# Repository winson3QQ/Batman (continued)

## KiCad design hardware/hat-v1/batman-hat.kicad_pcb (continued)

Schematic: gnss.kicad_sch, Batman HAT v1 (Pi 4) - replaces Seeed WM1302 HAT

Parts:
C80: 10u 10V; C_0603_1608Metric
C81: 100n 16V; C_0402_1005Metric
C82: 10n 16V; C_0402_1005Metric
C83: 47p C0G; C_0402_1005Metric
J4: U.FL; U.FL_Hirose_U.FL-R-SMT-1_Vertical; MPN U.FL-R-SMT-1(10)
JP6: GNSS (closed); SolderJumper-2_P1.3mm_Bridged_RoundedPad1.0x1.5mm
L80: 27nH; L_0402_1005Metric; MPN LQG15HS27NJ02D
R80: DNP 0R; R_0402_1005Metric; not fitted
R81: 68R; R_1206_3216Metric
U14: MAX-M10S-00B; ublox_MAX; MPN MAX-M10S-00B; not fitted

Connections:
3V3_GNSS: C80.1, C81.1, JP6.2, U14.6 (V_BCKP), U14.7 (VCC_IO), U14.8 (VCC); also elsewhere on the board
GND: C80.2, C81.2, C82.2, J4.2 (SHIELD), R80.2, U14.1 (GND), U14.10 (GND), U14.12 (GND); also elsewhere on the board
GNSS_ANT: C83.1, J4.1 (SIG), L80.2
GNSS_ANT_DET: U14.16 (SDA); also elsewhere on the board
GNSS_ANT_FEED: C82.1, L80.1, R81.2; also elsewhere on the board
GNSS_ANT_SHORT_N: U14.17 (SCL); also elsewhere on the board
GNSS_ANT_SUP: R81.1, U14.14 (VCC_RF); also elsewhere on the board
GNSS_LNA_EN: U14.13 (LNA_EN); also elsewhere on the board
GNSS_PPS: U14.4 (TIMEPULSE); also elsewhere on the board
GNSS_RFIN: C83.2, U14.11 (RF_IN)
GNSS_RST_N: U14.9 (~RESET); also elsewhere on the board
GNSS_SAFEBOOT_N: U14.18 (~SAFEBOOT); also elsewhere on the board
GNSS_VIOSEL: R80.1, U14.15 (VIO_SEL)
UART5_RX: U14.2 (TXD); also elsewhere on the board
UART5_TX: U14.3 (RXD); also elsewhere on the board

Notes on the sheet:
NOTES JP6: cut to isolate the GNSS supply (UART5_TX idle-high still back-feeds RXD) U14: UBX-20035208 R08: VIO_SEL open = 3.3 V I/O; V_BCKP 1.65-3.6 V; V_IO ramp >= 25 us/V; ext. gain <= 30 dB R80: leave NOT fitted: VIO_SEL to GND would select 1.8 V I/O (datasheet Table 10) R81: VCC_RF max 50 mA op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

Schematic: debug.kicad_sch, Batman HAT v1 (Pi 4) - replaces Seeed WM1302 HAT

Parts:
J5: Tag-Connect TC2050; Tag-Connect_TC2050-IDC-NL_2x05_P1.27mm_Vertical
R40, R41, R42, R43, R44, R45, R46, R47: 0R; R_0402_1005Metric
R48: 1k; R_0402_1005Metric
TP1: VBAT 6-17V; TestPoint_Keystone_5015_Micro-Minature
TP2: 5V 5.10-5.25; TestPoint_Keystone_5015_Micro-Minature
TP3: 3V3 HaLow 3.2-3.4; TestPoint_Keystone_5015_Micro-Minature
TP4: GND; TestPoint_Keystone_5015_Micro-Minature
TP5: VSYS 6-17V; TestPoint_Pad_D1.5mm
TP6: 5V_PI 5.0-5.2; TestPoint_Pad_D1.5mm
TP7: 3V3_BUCK 3.25-3.40; TestPoint_Pad_D1.5mm
TP8: 3V3_PI 3.2-3.4; TestPoint_Pad_D1.5mm
TP9: 3V3_SEC 3.2-3.4; TestPoint_Pad_D1.5mm
TP10: 3V3_GNSS 3.2-3.4; TestPoint_Pad_D1.5mm
TP11: VRTC 0-3.3; TestPoint_Pad_D1.5mm
TP12: GND; TestPoint_Pad_D1.5mm
TP13: GNSS_RST_N; TestPoint_Pad_D1.0mm
TP14: GNSS_SAFEBOOT_N; TestPoint_Pad_D1.0mm
TP15: GNSS_ANT_DET; TestPoint_Pad_D1.0mm
TP16: GNSS_ANT_SHORT_N; TestPoint_Pad_D1.0mm
TP17: PWR_BTN_N; TestPoint_Pad_D1.0mm
TP18: LTC_KILL_N; TestPoint_Pad_D1.0mm
TP19: LTC_ENB; TestPoint_Pad_D1.0mm
TP20: EN_5V; TestPoint_Pad_D1.0mm
TP21: EN_3V3; TestPoint_Pad_D1.0mm
TP22: PG_5V; TestPoint_Pad_D1.0mm
TP23: EF_FLT_N; TestPoint_Pad_D1.0mm
TP24: EF_SHDN; TestPoint_Pad_D1.0mm
TP25: RTC_CLKOUT; TestPoint_Pad_D1.0mm
TP26: RTC_INT_N; TestPoint_Pad_D1.0mm
TP27: K1+ (R9); TestPoint_Pad_D1.0mm
TP28: K1- (R9); TestPoint_Pad_D1.0mm
TP29: K2+ (R22); TestPoint_Pad_D1.0mm
TP30: K2- (R22); TestPoint_Pad_D1.0mm

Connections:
3V3_BUCK: TP7.1, TP29.1; also elsewhere on the board
3V3_GNSS: TP10.1; also elsewhere on the board
3V3_MPCIE: TP3.1; also elsewhere on the board
3V3_SEC: TP9.1; also elsewhere on the board
3V3_SH: TP30.1; also elsewhere on the board
5V_BUCK: TP2.1; also elsewhere on the board
CONSOLE_RX: R41.1; also elsewhere on the board
CONSOLE_TX: R40.1; also elsewhere on the board
EF_FLT_N: TP23.1; also elsewhere on the board
EF_OUT: TP27.1; also elsewhere on the board
EF_SHDN: TP24.1; also elsewhere on the board
EN_5V: TP20.1; also elsewhere on the board
GND: J5.3, TP4.1, TP12.1; also elsewhere on the board
GNSS_ANT_DET: TP15.1; also elsewhere on the board
GNSS_ANT_SHORT_N: TP16.1; also elsewhere on the board
GNSS_RST_N: TP13.1; also elsewhere on the board
GNSS_SAFEBOOT_N: TP14.1; also elsewhere on the board
HALOW_BUSY: R47.1; also elsewhere on the board
HALOW_IRQ: R46.1; also elsewhere on the board
LTC_ENB: TP19.1; also elsewhere on the board
LTC_KILL_N: TP18.1; also elsewhere on the board
PG_5V: TP22.1; also elsewhere on the board
PWR_BTN_N: TP17.1; also elsewhere on the board
RTC_CLKOUT: TP25.1; also elsewhere on the board
RTC_INT_N: TP26.1; also elsewhere on the board
SPI0_CE0: R45.1; also elsewhere on the board
SPI0_MISO: R44.1; also elsewhere on the board
SPI0_MOSI: R43.1; also elsewhere on the board
SPI0_SCLK: R42.1; also elsewhere on the board
TC_3V3: J5.1, R48.2
TC_BUSY: J5.10, R47.2
TC_CS: J5.8, R45.2
TC_IRQ: J5.9, R46.2
TC_MISO: J5.7, R44.2
TC_MOSI: J5.6, R43.2
TC_RX: J5.4, R41.2
TC_SCLK: J5.5, R42.2
TC_TX: J5.2, R40.2
VBAT_RAW: TP1.1; also elsewhere on the board
VRTC: TP11.1; also elsewhere on the board
VSYS: TP5.1, TP28.1; also elsewhere on the board

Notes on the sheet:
NOTES J5: console = passwordless root until #137 ships: release gate R48: sense only: an adapter that drives VCC cannot back-feed the Pi R40: R40-R47 debug links: fitted on dev boards, NOT fitted on production (HaLow keys cross SPI0) TP27: Kelvin pads on the shunts: R9 mV x 100 = mA, R22 mV x 50 = 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

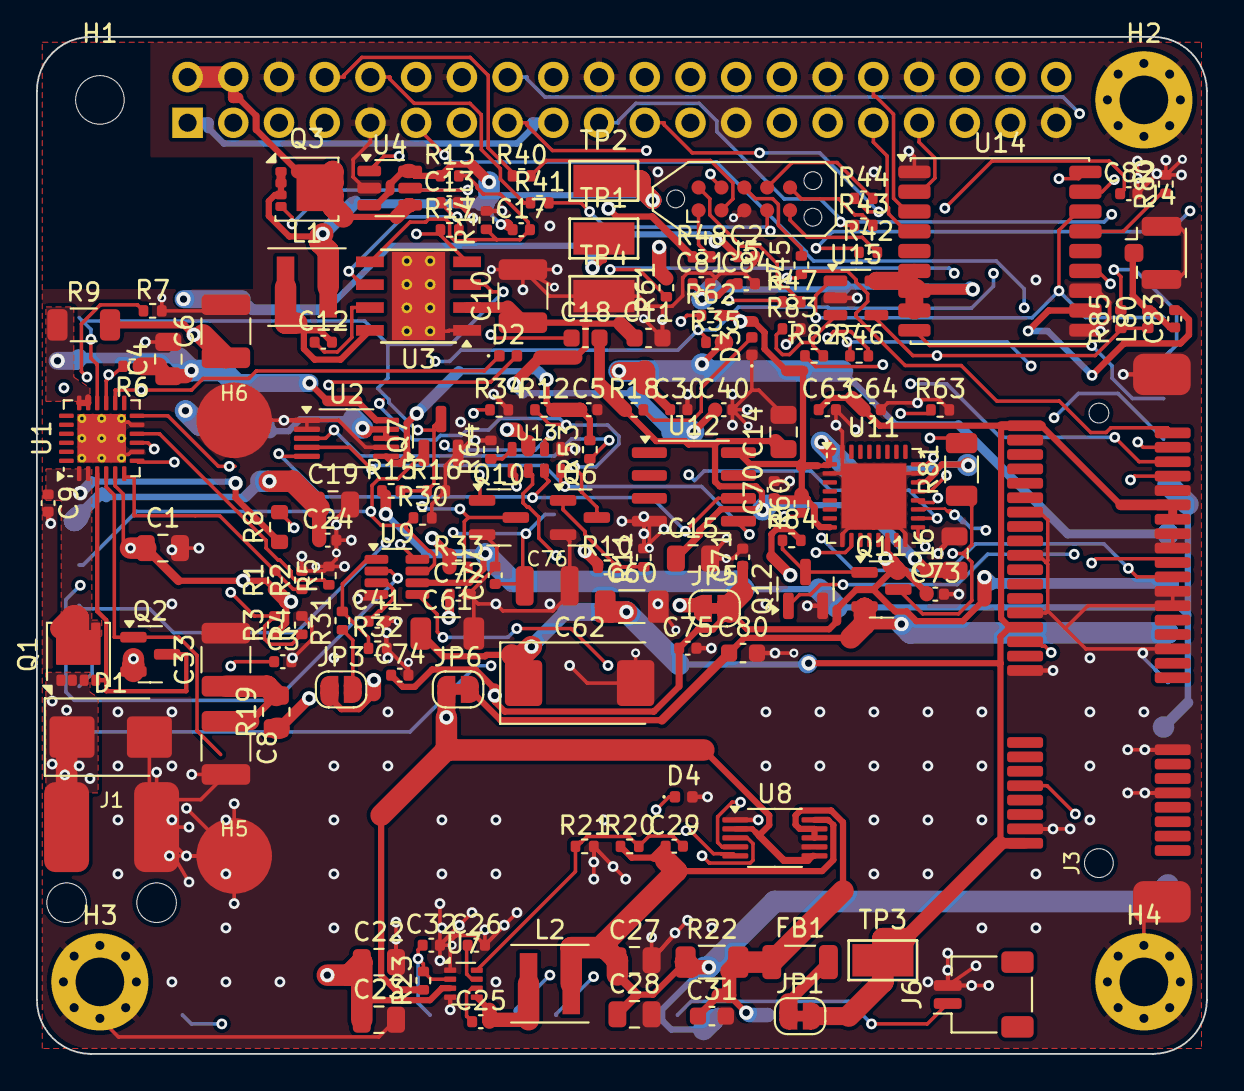
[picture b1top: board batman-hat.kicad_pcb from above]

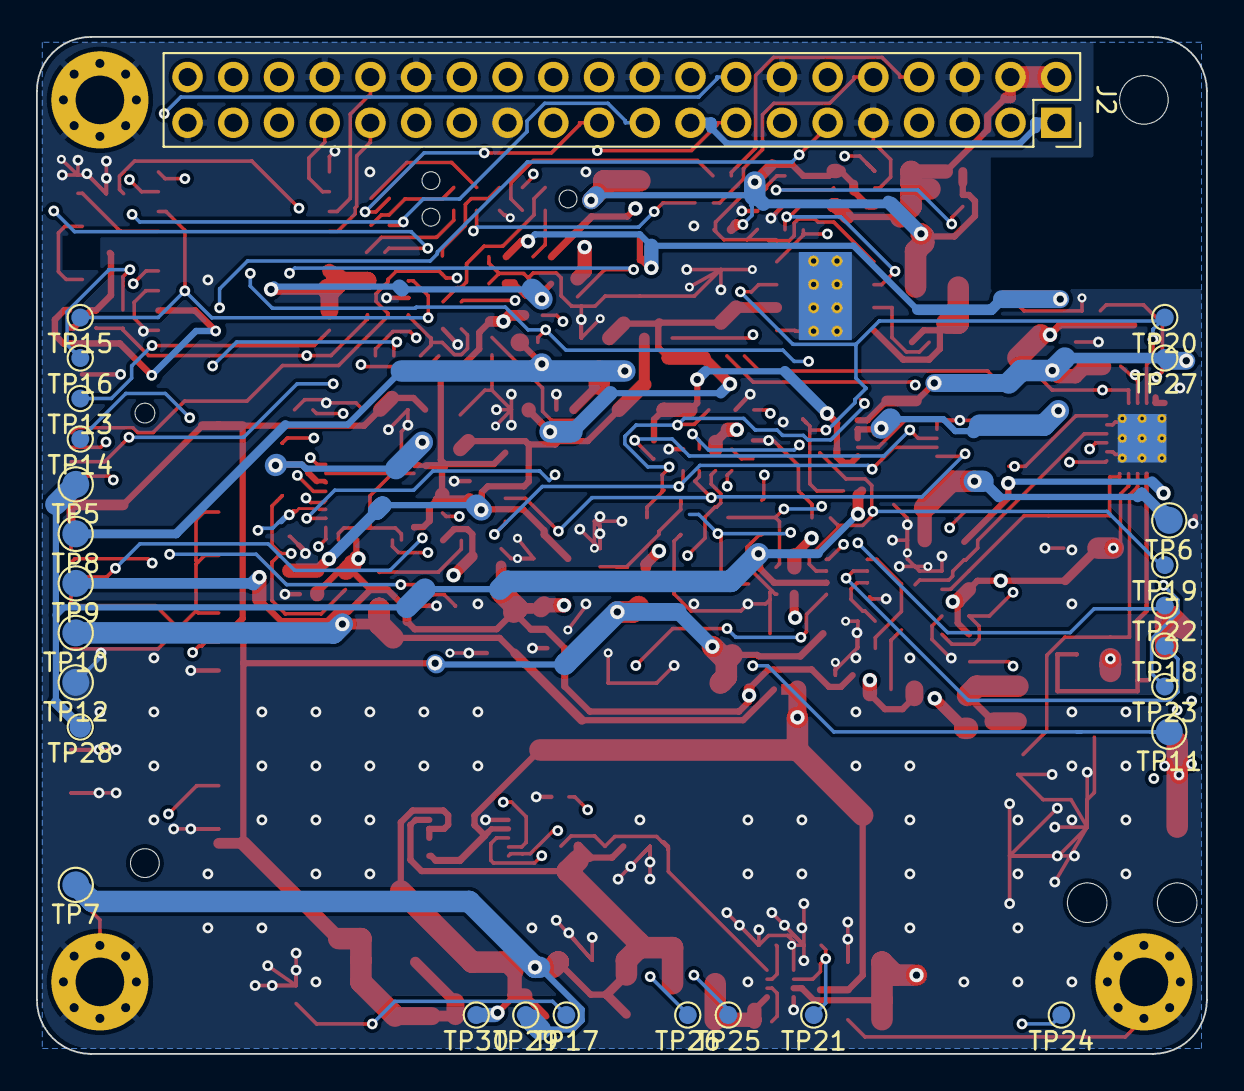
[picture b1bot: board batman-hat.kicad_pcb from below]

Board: 4 copper layers, 65.0 x 56.5 mm, 174 parts (27 on the bottom side), 97 nets.

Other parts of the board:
C84: 100n 16V; C_0402_1005Metric
Q11: Si2301CDS; SOT-23
Q12: BSS138; SOT-23
R82: 560R; R_0402_1005Metric
R83, R84: 100k; R_0402_1005Metric
R85: 1k; R_0402_1005Metric
U15: OPA333AIDBVR; SOT-23-5

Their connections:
3V3_GNSS: C84.1, Q11.2, R84.2, U15.5; also elsewhere on the board
GND: C84.2, Q12.2, R83.2, U15.2; also elsewhere on the board
GNSS_ANT_DET: U15.1; also elsewhere on the board
GNSS_ANT_FEED: R85.1, U15.4; also elsewhere on the board
GNSS_ANT_SHORT_N: R85.2; also elsewhere on the board
GNSS_ANT_SUP: Q11.3, R82.1; also elsewhere on the board
GNSS_ANT_VREF: R82.2, R83.1, U15.3
GNSS_LNA_EN: Q12.1; also elsewhere on the board
GNSS_T1G: Q11.1, Q12.3, R84.1

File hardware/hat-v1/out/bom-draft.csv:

Refs,Qty,Value,Footprint,MPN,Manufacturer,Tier,LCSC,Assembly,Note
"C1,C4",2,1u 50V X7R,C_0805_2012Metric,,,C,,JLCPCB,
"C2,C9,C40",3,100n 50V X7R,C_0402_1005Metric,,,C,,JLCPCB,
C3,1,22n 16V X7R,C_0402_1005Metric,,,C,,JLCPCB,2.27 V/ms soft start
"C5,C12,C24,C25,C30,C63,C64,C70,C71,C72,C74,C75,C77,C81,C84",15,100n 16V,C_0402_1005Metric,,,C,,JLCPCB,
"C6,C8,C10,C33",4,10u 50V X7R,C_1210_3225Metric,,,C,,JLCPCB,
C11,1,220n 50V X7R,C_0603_1608Metric,,,C,,JLCPCB,hot-loop cap: closest to VIN/PGND
"C13,C41,C73",3,1u 10V,C_0402_1005Metric,,,C,,JLCPCB,
"C14,C15,C16,C19,C22,C23,C27,C28",8,22u 10V X5R,C_0805_2012Metric,,,C,,JLCPCB,
"C17,C29",2,DNP 22p,C_0402_1005Metric,,,C,,DNP,optional feed-forward (datasheet 9.2.2.8)
C18,1,220n 25V X7R,C_0603_1608Metric,,,C,,JLCPCB,
C26,1,22n 16V,C_0402_1005Metric,,,C,,JLCPCB,soft start ~3.2 ms
C31,1,10u 10V X5R,C_0603_1608Metric,,,C,,JLCPCB,pi-filter input cap
C32,1,2.2n 16V,C_0402_1005Metric,,,C,,JLCPCB,EN has only a 0.7 uA pull-up: noise immunity
"C60,C61",2,47u 6.3V X5R,C_1206_3216Metric,,,C,,JLCPCB,
C62,1,220u 6.3V polymer,CP_EIA-7343-20_Kemet-V,T520V227M006ATE015,KEMET,C,,JLCPCB,7343-20: <=1.9 mm tall; absorbs HaLow TX bursts
C76,1,CPH3225A 11mF,Seiko_CPH3225A,CPH3225A,Seiko Instruments,C,,JLCPCB,"RTC backup (user decision 2026-09-27: supercap, GPS re-syncs after ~2 days off). Internal trickle path has a Schottky (0.25 V) -> charges to ~3.05 V, below the 3.3 V rating"
C80,1,10u 10V,C_0603_1608Metric,,,C,,JLCPCB,
C82,1,10n 16V X7R,C_0402_1005Metric,,,C,,JLCPCB,C14: bias-T capacitor (Table 52)
C83,1,47p C0G,C_0402_1005Metric,,,C,,JLCPCB,C18: DC block 47 pF 5 % C0G (Table 52)
D1,1,SMBJ20CA,D_SMB,SMBJ20CA,Littelfuse,C,,JLCPCB,bidirectional: survives reversed battery
D2,1,RED,LED_0402_1005Metric,,,C,,JLCPCB,eFuse fault LED (on = fault)
D3,1,GREEN,LED_0402_1005Metric,,,C,,JLCPCB,HAT 5 V buck running
D4,1,TPD1E10B06,D_0402_1005Metric,TPD1E10B06DPYR,TI,C,,JLCPCB,ESD for the panel button wire
FB1,1,600R@100MHz >=4A,L_1206_3216Metric,BLM31KN601SN1L,Murata,C,,JLCPCB,"verify rating at BOM step: >=4 A, <=30 mOhm"
J2,1,"Pi 40-pin (female, 11 mm stack)",PinSocket_2x20_P2.54mm_Vertical,,,C,,JLCPCB,through-hole on the bottom side; 8.5 mm socket for 11 mm standoffs
J3,1,mPCIe 5.2H,MiniPCIe_Lianxin_XDMP-052-A01_H5.2,XDMP-052-A01,Lianxin (China),C,C7498130,JLCPCB,pin 8 UIM_PWR not connected on the card -> GPIO18 freed for the TPM
J4,1,U.FL,U.FL_Hirose_U.FL-R-SMT-1_Vertical,U.FL-R-SMT-1(10),Hirose,C,,JLCPCB,active patch antenna with SAW pre-filter; 50 ohm CPWG trace
J6,1,PANEL BTN,JST_SH_SM02B-SRSS-TB_1x02-1MP_P1.00mm_Horizontal,SM02B-SRSS-TB,JST,C,,JLCPCB,to the IP67 panel push-button. No on-board button (user decision): on the bench plug a button here or short the PWR_BTN_N back-side pad to GND
L1,1,3.3uH Isat>=5.5A,L_Coilcraft_XxL4030,XGL4030-332MEC,Coilcraft,C,,JLCPCB,height <=3.1 mm; alternative: Wurth WE-XHMI 4030
L2,1,2.2uH Isat>=5.8A,L_Coilcraft_XxL4030,XGL4030-222MEC,Coilcraft,C,,JLCPCB,
L80,1,27nH,L_0402_1005Metric,LQG15HS27NJ02D,Murata,C,,JLCPCB,"L3: bias-T inductor, >500 ohm at L1, >=300 mA (Table 54)"
Q1,1,CSD19537Q3,VSON-8_3.3x3.3mm_P0.65mm_NexFET,CSD19537Q3,TI,C,,JLCPCB,reverse-polarity blocking FET (TPS2663 datasheet Fig 9-2)
"Q2,Q6,Q7,Q10,Q12",5,BSS138,SOT-23,BSS138,onsemi (not Nexperia),C,,JLCPCB,"B_GATE fast pull-down: Vds>=15V, Vgs max 20V, Ciss<=50pF, Vth(min)<=3V"
Q3,1,CSD17578Q3A,VSON-8_3.3x3.3mm_P0.65mm_NexFET,CSD17578Q3A,TI,C,,JLCPCB,"30 V, low Rds(on); ideal-diode FET"
Q11,1,Si2301CDS,SOT-23,SI2301CDS-T1-GE3,Vishay,C,,JLCPCB,T1: antenna supply switch (reference uses Vishay Si1016X; any small P-FET)
"R1,R6",2,383k 1%,R_0402_1005Metric,,,C,,JLCPCB,
"R2,R4,R7,R32",4,100k 1%,R_0402_1005Metric,,,C,,JLCPCB,
R3,1,1.50M 1%,R_0402_1005Metric,,,C,,JLCPCB,"OVP 19.2 V typ (18.8-19.6), release >=17.44 V: full 4S 16.8 V never latches off (review P3)"
R5,1,3.57k 1%,R_0402_1005Metric,,,C,,JLCPCB,I_OL = 18k/R = 5.0 A
R8,1,4.7k,R_0603_1608Metric,,,C,,JLCPCB,LED fed from EF_IN: protected from reverse battery
R9,1,10m 1% 0.5W,R_1206_3216Metric,,,C,,JLCPCB,INA226 #1 shunt; route IN+/IN- as Kelvin traces from the pads
"R10,R11,R30",3,1M,R_0402_1005Metric,,,C,,JLCPCB,1M/1M: 9 uA standby drain
"R12,R33,R35,R53,R60,R61,R62,R63",8,10k,R_0402_1005Metric,,,C,,JLCPCB,
R13,1,100k 0.5%,R_0402_1005Metric,,,C,,JLCPCB,
R14,1,24.0k 0.5%,R_0402_1005Metric,,,C,,JLCPCB,Vout = 1.0 V x (1 + 100/24) = 5.17 V
R15,1,102k 1%,R_0402_1005Metric,,,C,,JLCPCB,
R16,1,24.3k 1%,R_0402_1005Metric,,,C,,JLCPCB,EN UVLO: 6.40 V on / 5.88 V off
"R17,R23,R34,R64,R83,R84",6,100k,R_0402_1005Metric,,,C,,JLCPCB,
R18,1,2.2k,R_0402_1005Metric,,,C,,JLCPCB,
R19,1,0.47R,R_0805_2012Metric,,,C,,JLCPCB,RC damper for hot-plug ringing: 0.47R + 2x10uF keeps a 16.8 V plug-in below OVP (sim S1)
R20,1,31.6k 1%,R_0402_1005Metric,,,C,,JLCPCB,
R21,1,10.0k 1%,R_0402_1005Metric,,,C,,JLCPCB,Vout = 0.8 V x (1 + 31.6/10) = 3.33 V
R22,1,20m 1% 0.5W,R_1206_3216Metric,,,C,,JLCPCB,"INA226 #2 shunt, upstream of every socket bulk cap"
R31,1,787k 1%,R_0402_1005Metric,,,C,,JLCPCB,AUTO-ON 7.10 V typ / 6.74 V min: above the 5 V buck EN max 6.55 V (review P1)
"R40,R41,R42,R43,R44,R45,R46,R47",8,0R,R_0402_1005Metric,,,C,,JLCPCB,"R40-R47 debug links: fitted on dev boards, NOT fitted on production (HaLow keys cross SPI0)"
"R48,R85",2,1k,R_0402_1005Metric,,,C,,JLCPCB,sense only: an adapter that drives VCC cannot back-feed the Pi
R80,1,DNP 0R,R_0402_1005Metric,,,C,,DNP,leave NOT fitted: VIO_SEL to GND would select 1.8 V I/O (datasheet Table 10)
R81,1,10R,R_1206_3216Metric,,,C,,JLCPCB,R8: current sense / short limiter 10 ohm 0.25 W (Table 53); ~18.5 mV per 1.85 mA
R82,1,560R,R_0402_1005Metric,,,C,,JLCPCB,R5 (Table 53)
TP1,1,VBAT 6-17V,TestPoint_Keystone_5015_Micro-Minature,,,C,,JLCPCB,
TP2,1,5V 5.10-5.25,TestPoint_Keystone_5015_Micro-Minature,,,C,,JLCPCB,
TP3,1,3V3 HaLow 3.2-3.4,TestPoint_Keystone_5015_Micro-Minature,,,C,,JLCPCB,
TP4,1,GND,TestPoint_Keystone_5015_Micro-Minature,,,C,,JLCPCB,
U1,1,TPS26631RGER,Texas_RGE0024H_VQFN-24-1EP_4x4mm_P0.5mm_EP2.7x2.7mm_ThermalVias,TPS26631RGER,TI,B,,JLCPCB,MODE=GND auto-retry; SHDN floats (2.7 V open-circuit) = enabled; IMON unused
"U2,U8",2,INA226AIDGSR,VSSOP-10_3x3mm_P0.5mm,INA226AIDGSR,TI,B,,JLCPCB,I2C 0x40 (A0=A1=GND): whole-node current + battery voltage
U3,1,LMR33640DDDAR,Texas_HSOP-8-1EP_3.9x4.9mm_P1.27mm_ThermalVias,LMR33640DDDAR,TI,B,,JLCPCB,"1 MHz, 4 A"
U4,1,LM74700QDBVRQ1,SOT-23-6,LM74700QDBVRQ1,TI,B,,JLCPCB,HAT back-power rule: Pi USB-C cannot feed into the HAT 5 V buck
U7,1,TPS62933FDRLR,SOT-583-8,TPS62933FDRLR,TI,B,,JLCPCB,FCCM fixed 1.2 MHz (RT=GND); EN abs max 6 V -> open-drain pull-down only
U9,1,LTC2955ITS8-2#TRPBF,TSOT-23-8,LTC2955ITS8-2#TRPBF,Analog Devices,B,,JLCPCB,-2 = active-low EN-bar (900k to VIN when off); KILL blanking 304-720 ms
U11,1,SLB9672XU2.0,QFN-32-1EP_5x5mm_P0.5mm_EP3.6x3.6mm,SLB9672XU2.0 (orderable code: verify at M3),Infineon,A,,fit in Taiwan (Tier A),NC 6/29/30 must float; GPIO 3/4/7 have internal pull-ups; NO test points on TPM nets
U12,1,ATECC608C-TFLXTLS,SOIC-8_3.9x4.9mm_P1.27mm,ATECC608C-TFLXTLS (SOIC-8 suffix: verify at M3),Microchip,A,,fit in Taiwan (Tier A),I2C 0x36 (TrustFLEX)
U13,1,RV-3028-C7,MicroCrystal_RV-3028-C7,RV-3028-C7 32.768kHz 1ppm TA QC,Micro Crystal,A,,fit in Taiwan (Tier A),"I2C 0x52. App Manual: CLKOUT 32.768 kHz ON by default -> disable in EEPROM (FD=111); backup mode LSM (BSM=11) because VBACKUP ~3.05 V is close to VDD (DSM not recommended, sec 4.2.2)"
U14,1,MAX-M10S-00B,ublox_MAX,MAX-M10S-00B,u-blox,A,,fit in Taiwan (Tier A),UBX-20035208 R08: VIO_SEL open = 3.3 V I/O; V_BCKP 1.65-3.6 V; ext. gain <= 30 dB. SDA/SCL reused as ANT_DETECT/ANT_SHORT_N: CFG-I2C-ENABLED=0 (Integration manual Table 50)
U15,1,OPA333AIDBVR,SOT-23-5,OPA333AIDBVR,TI,B,,JLCPCB,"U6 comparator (reference: LT6000/LT6003); zero-drift RRIO, offset <= 10 uV vs an 18.5 mV threshold"

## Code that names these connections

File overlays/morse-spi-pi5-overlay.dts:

/dts-v1/;
/plugin/;

/* Wio-WM6108 (MM6108) over SPI0 -- Raspberry Pi 5 / Pi 500 (BCM2712 + RP1).
 *
 * The BCM2711 version of this overlay re-uses the base DTB's `spi0_pins` node and
 * only overrides `brcm,pull`.  On BCM2712 that node does not exist, so the overlay
 * *creates* it with a pull setting and no `brcm,pins`/`brcm,function` -- the result
 * is a pinctrl map that mentions no pins at all and GPIO9/10/11 are never muxed to
 * SPI0 (verified with `pinctrl get 9-11`: "none").  MISO then floats and every
 * transfer reads 0xFF, which the driver reports as CMD53 -EPROTO / CMD63 -ENODATA.
 *
 * Here we point pinctrl-0 at RP1's own `rp1_spi0_gpio9` node instead.  GPIO8 stays a
 * plain GPIO chip-select (cs-gpios), so it is NOT included in the SPI0 function group.
 */

/ {
	compatible = "brcm,bcm2712";

	fragment@0 {
		target = <&spi0>;

		__overlay__ {
			pinctrl-names = "default";
			pinctrl-0 = <&rp1_spi0_gpio9 &mm_spi0_cs_pins>;
			cs-gpios = <&gpio 8 1>;  /* GPIO8, active low */
			#address-cells = <1>;
			#size-cells = <0>;
			status = "okay";

			mm6108@0 {
				compatible = "morse,mm610x-spi";
				reg = <0>;
				reset-gpios = <&gpio 17 0>;     /* GPIO17, active high */
				power-gpios = <&gpio 23 0       /* GPIO23 wakeup, active high */
				               &gpio 24 0>;     /* GPIO24 busy, active high */
				spi-irq-gpios = <&gpio 5 0>;    /* GPIO5, active high */
				spi-max-frequency = <20000000>; /* 20 MHz */
				status = "okay";
			};

			spidev@0 {
				reg = <0>;
				status = "disabled";
			};

			spidev@1 {
				reg = <1>;
				status = "disabled";
			};
		};
	};

	fragment@1 {
		target = <&gpio>;

		__overlay__ {
			mm_spi0_cs_pins: mm_spi0_cs_pins {
				pins = "gpio8";
				function = "gpio";
				bias-pull-up;
				output-high;    /* chip-select deasserted */
			};
		};
	};
};
